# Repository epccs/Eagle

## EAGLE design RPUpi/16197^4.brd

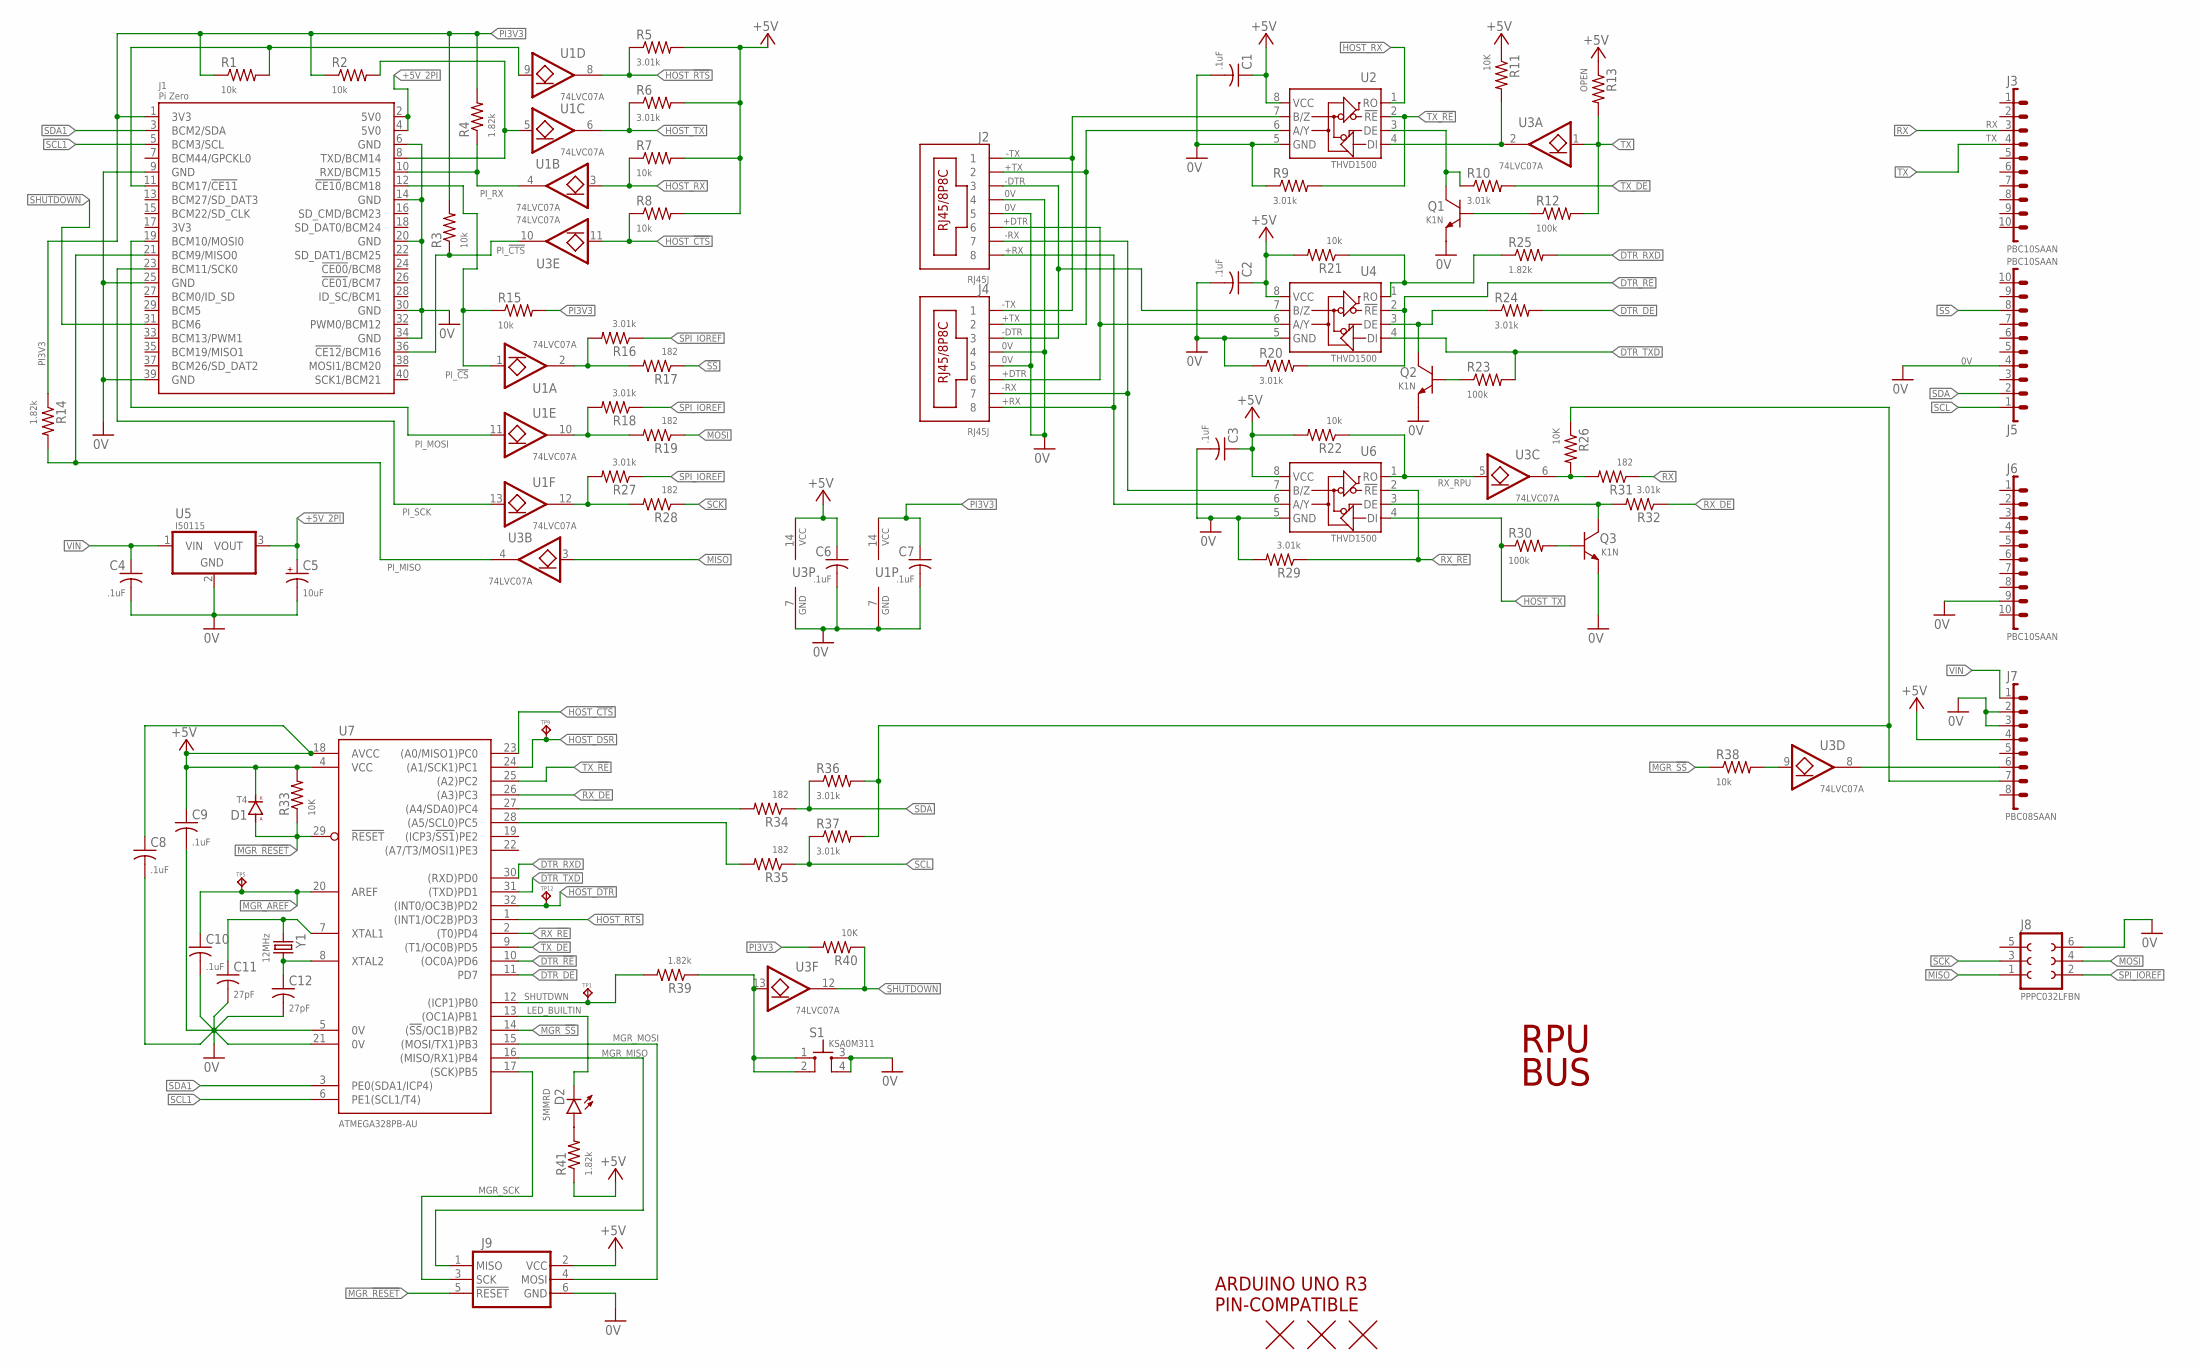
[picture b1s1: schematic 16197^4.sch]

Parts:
C1, C2, C3, C4, C6, C7, C8, C9, C10: .1uF; C0603(1608)
C5: 10uF; 3216
C11, C12: 27pF; C0603(1608)
D1: T4; SOD123
D2: 5MMRD; LED5MM
J1: Pi Zero; RASPI_ZERO_V40PIN
J2, J4: RJ45J; RJ45-8HZT
J3, J5, J6: PBC10SAAN; 1X10
J7: PBC08SAAN; 1X8
J8: PPPC032LFBN; F2X3
J9: ISP-SPIPTH; ISP
Q1, Q2, Q3: K1N; SOT23
R1, R2, R3, R7, R8, R15, R21, R22, R38: 10k; C0805(2012)
R4, R14, R25, R39, R41: 1.82k; C0805(2012)
R5, R6, R9, R10, R16, R18, R20, R24, R27, R29, R32, R36, R37: 3.01k; C0805(2012)
R11, R26, R33, R40: 10K; C0805(2012)
R12, R23, R30: 100k; C0805(2012)
R13: OPEN; C0805(2012)
R17, R19, R28, R31, R34, R35: 182; C0805(2012)
S1: KSA0M311; 0M311
TP1, TP5, TP9, TP12: TPPAD1-08; P1-08
U1, U3: 74LVC07A; 14SOIC
U2, U4, U6: THVD1500; SOIC8
U5: I50115; OKI-78SR-H
U7: ATMEGA328PB-AU; TQFP32-08
U$1: ARDUINO-UNO; ARDUINO_UNO
U$2, U$3, U$4: FIDUCIAL1.27; FIDUCIAL-1.27
Y1: 12MHz; CSM-3X

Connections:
0V: C1.2, C2.2, C3.2, C4.2, C5.-, C6.2, C7.2, C8.2, C9.2, C10.2, C11.2, C12.2, J1.6 (GND), J1.9 (GND), J1.14 (GND), J1.20 (GND), J1.25 (GND), J1.30 (GND), J1.34 (GND), J1.39 (GND), J2.4, J2.5, J4.4, J4.5, J5.4, J6.9, J7.2, J7.3, J8.6, J9.6 (GND), Q1.E, Q2.E, Q3.E, R9.1, R20.1, R29.2, S1.3, S1.4, U1.7 (GND), U2.5 (GND), U3.7 (GND), U4.5 (GND), U5.2 (GND), U6.5 (GND), U7.5 (0V), U7.21 (0V)
!RESET: J7.6, U3.8 (O)
!SS: J5.8, R17.1
+5V: C1.1, C2.1, C3.1, C6.1, C8.1, C9.1, D1.C (K), J7.4, J9.2 (VCC), R5.2, R6.2, R7.2, R8.2, R11.1, R13.1, R21.2, R22.2, R33.2, R41.1, U2.8 (VCC), U3.14 (VCC), U4.8 (VCC), U6.8 (VCC), U7.4 (VCC), U7.18 (AVCC)
+5V_2PI: C5.+, J1.2 (5V0), J1.4 (5V0), U5.3 (VOUT)
+DTR: J2.6, J4.6, U4.6 (A/Y)
+RX: J2.8, J4.8, U6.6 (A/Y)
+TX: J2.2, J4.2, U2.6 (A/Y)
-DTR: J2.3, J4.3, U4.7 (B/Z)
-RX: J2.7, J4.7, U6.7 (B/Z)
-TX: J2.1, J4.1, U2.7 (B/Z)
DTR_!RE: R20.2, U4.2 (!RE), U7.10 ((OC0A)PD6)
DTR_DE: R24.2, U7.11 (PD7)
DTR_RXD: R25.2, U7.30 ((RXD)PD0)
DTR_TXD: R23.2, U4.4 (DI), U7.31 ((TXD)PD1)
HOST_!CTS: R8.1, U3.11 (I), U7.23 ((A0/MISO1)PC0)
HOST_!DSR: TP9.TP, U7.24 ((A1/SCK1)PC1)
HOST_!DTR: TP12.TP, U7.32 ((INT0/OC3B)PD2)
HOST_!RTS: R5.1, U1.8 (O), U7.1 ((INT1/OC2B)PD3)
HOST_RX: R7.1, U1.3 (I), U2.1 (RO)
HOST_TX: R6.1, R30.1, U1.6 (O), U6.4 (DI)
IOREF: J7.7, R26.1, R36.2, R37.2
LED_BUILTIN: D2.K, U7.13 ((OC1A)PB1)
MGR_!RESET: D1.A, J9.5 (!RESET), R33.1, U7.29 (!RESET)
MGR_!SS!: R38.1, U7.14 ((!SS!/OC1B)PB2)
MGR_AREF: C10.1, TP5.TP, U7.20 (AREF)
MGR_MISO: J9.1 (MISO), U7.16 ((MISO/RX1)PB4)
MGR_MOSI: J9.4 (MOSI), U7.15 ((MOSI/TX1)PB3)
MGR_SCK: J9.3 (SCK), U7.17 ((SCK)PB5)
MISO: J8.1, U3.3 (I)
MOSI: J8.4, R19.1
unnamed: J1.8 (TXD/BCM14), R2.2, U1.5 (I)
unnamed: R38.2, U3.9 (I)
unnamed: R34.2, U7.27 ((A4/SDA0)PC4)
unnamed: J1.11 (BCM17/!CE11!), R1.2, U1.9 (I)
unnamed: R27.2, R28.2, U1.12 (O)
unnamed: R18.2, R19.2, U1.10 (O)
unnamed: R39.1, S1.1, S1.2, U3.13 (I)
unnamed: R35.2, U7.28 ((A5/SCL0)PC5)
unnamed: R16.2, R17.2, U1.2 (O)
unnamed: R26.2, R31.2, U3.6 (O)
unnamed: Q3.C, R32.2, U6.3 (DE)
unnamed: Q1.B, R12.1
unnamed: Q1.C, R10.1, U2.3 (DE)
unnamed: R21.1, R25.1, U4.1 (RO)
unnamed: Q2.C, R24.1, U4.3 (DE)
unnamed: Q2.B, R23.1
unnamed: Q3.B, R30.2
unnamed: D2.A, R41.2
PI3V3: C7.1, J1.1 (3V3), R1.1, R2.1, R3.2, R4.2, R14.1, R15.2, R40.2, U1.14 (VCC)
PI_!CS: J1.12 (!CE10!/BCM18), R15.1, U1.1 (I)
PI_!CTS: J1.36 (!CE12!/BCM16), R3.1, U3.10 (O)
PI_MISO: J1.21 (BCM9/MISO0), R14.2, U3.4 (O)
PI_MOSI: J1.19 (BCM10/MOSI0), U1.11 (I)
PI_RX: J1.10 (RXD/BCM15), R4.1, U1.4 (O)
PI_SCK: J1.23 (BCM11/SCK0), U1.13 (I)
RX: J3.3, R31.1
RX_!RE: R29.1, U6.2 (!RE), U7.2 ((T0)PD4)
RX_DE: R32.1, U7.26 ((A3)PC3)
RX_RPU: R22.1, U3.5 (I), U6.1 (RO)
SCK: J8.3, R28.1
SCL: J5.1, R35.1, R37.1
SCL1: J1.5 (BCM3/SCL), U7.6 (PE1(SCL1/T4))
SDA: J5.2, R34.1, R36.1
SDA1: J1.3 (BCM2/SDA), U7.3 (PE0(SDA1/ICP4))
SHUTDOWN: J1.31 (BCM6), R40.1, U3.12 (O)
SHUTDWN: R39.2, TP1.TP, U7.12 ((ICP1)PB0)
SPI_IOREF: J8.2, R16.1, R18.1, R27.1
TX: J3.4, R12.2, R13.2, U3.1 (I)
TX_!RE: R9.2, U2.2 (!RE), U7.25 ((A2)PC2)
TX_DE: R10.2, U7.9 ((T1/OC0B)PD5)
TX_RPU: R11.2, U2.4 (DI), U3.2 (O)
VIN: C4.1, J7.1, U5.1 (VIN)
XTAL1: C11.1, U7.7 (XTAL1), Y1.1
XTAL2: C12.1, U7.8 (XTAL2), Y1.2

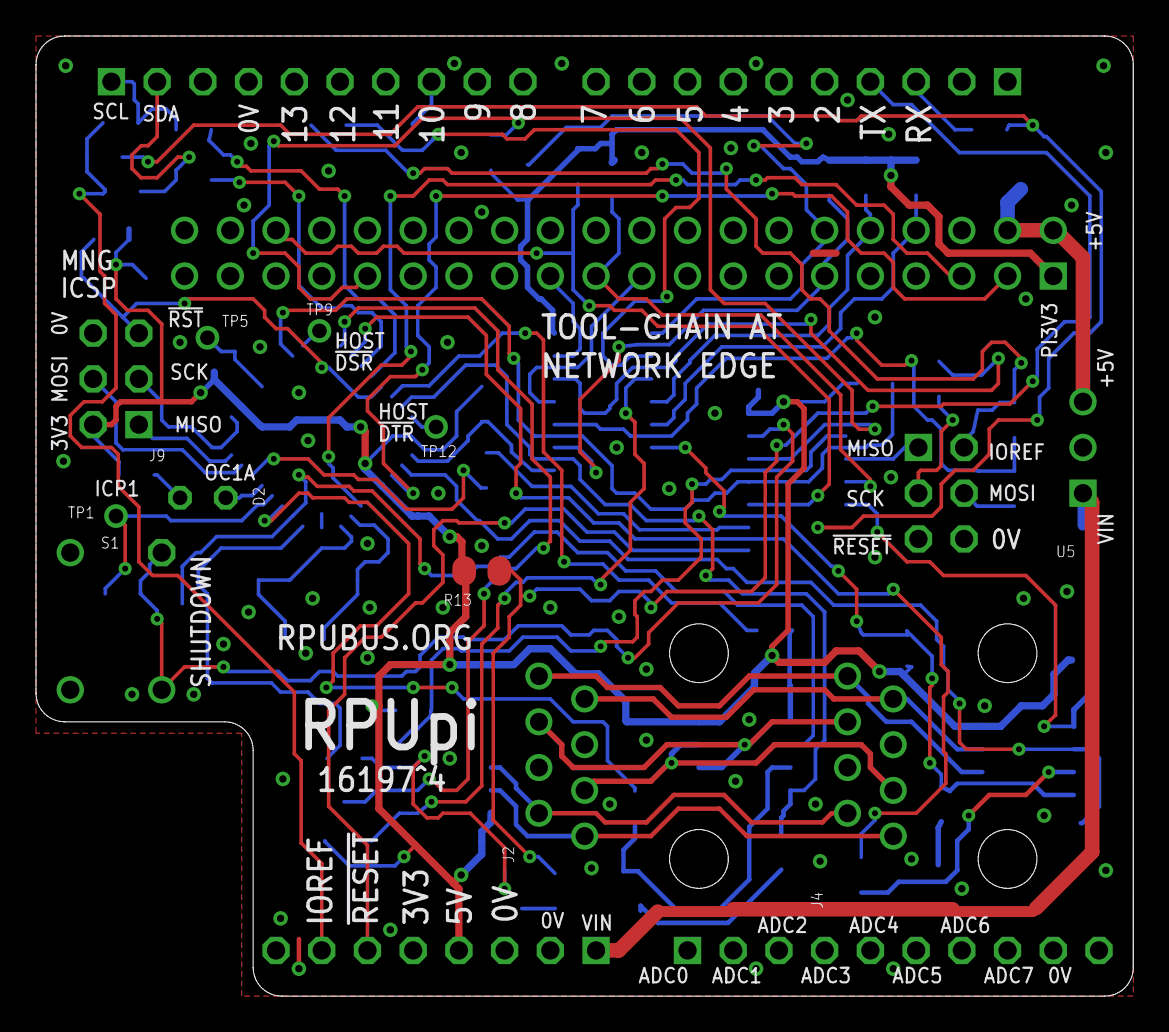
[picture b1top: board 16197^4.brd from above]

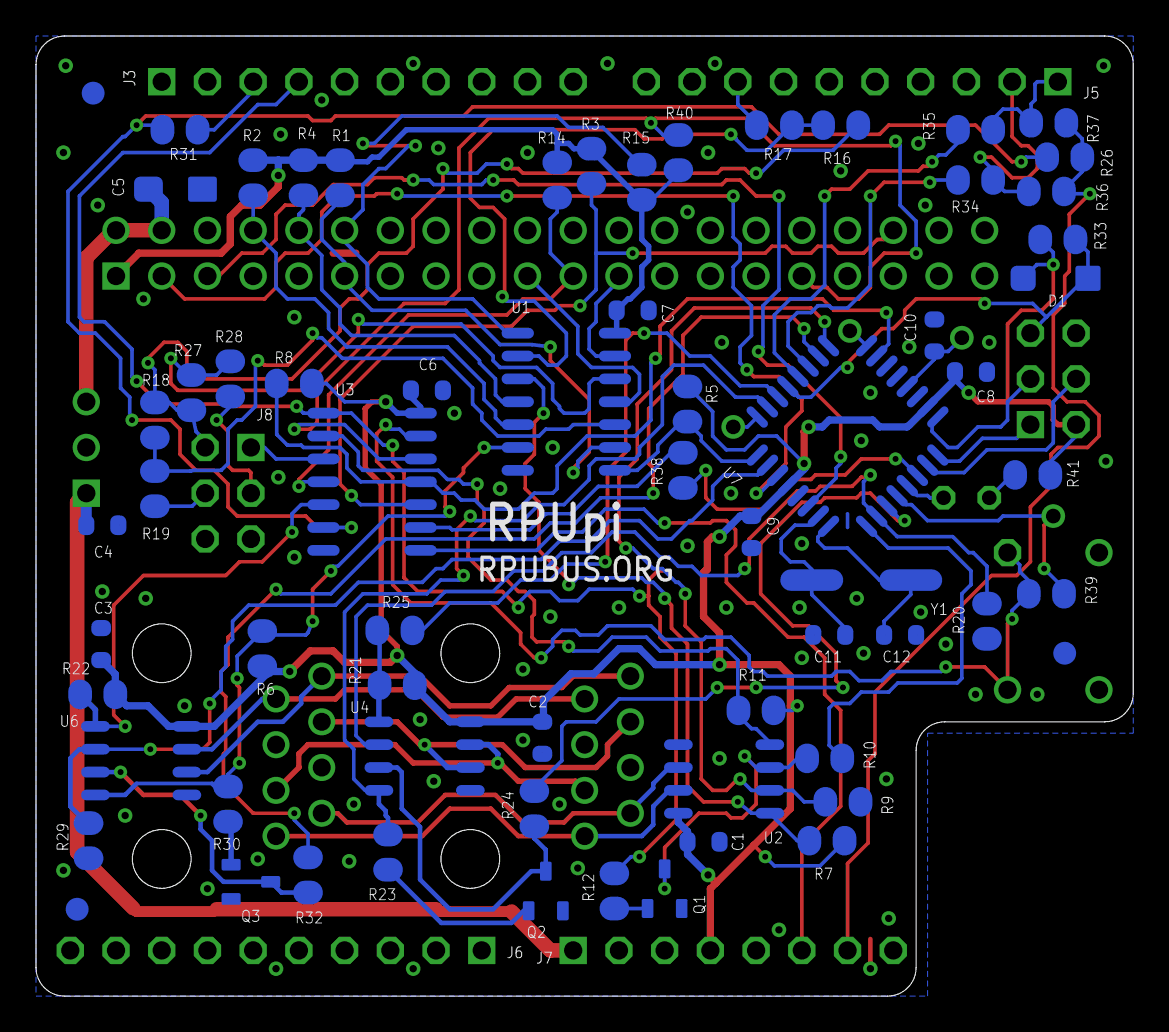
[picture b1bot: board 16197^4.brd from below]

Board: 2 copper layers, 61.0 x 53.3 mm, 84 parts (71 on the bottom side), 75 nets.

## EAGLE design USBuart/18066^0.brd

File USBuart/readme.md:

[USBuart]

USB UART bridge.

[USBuart]: https://github.com/epccs/Driver/tree/master/USBuart

The software for this will use the RPUftdi repo which will be renamed to USBuart.

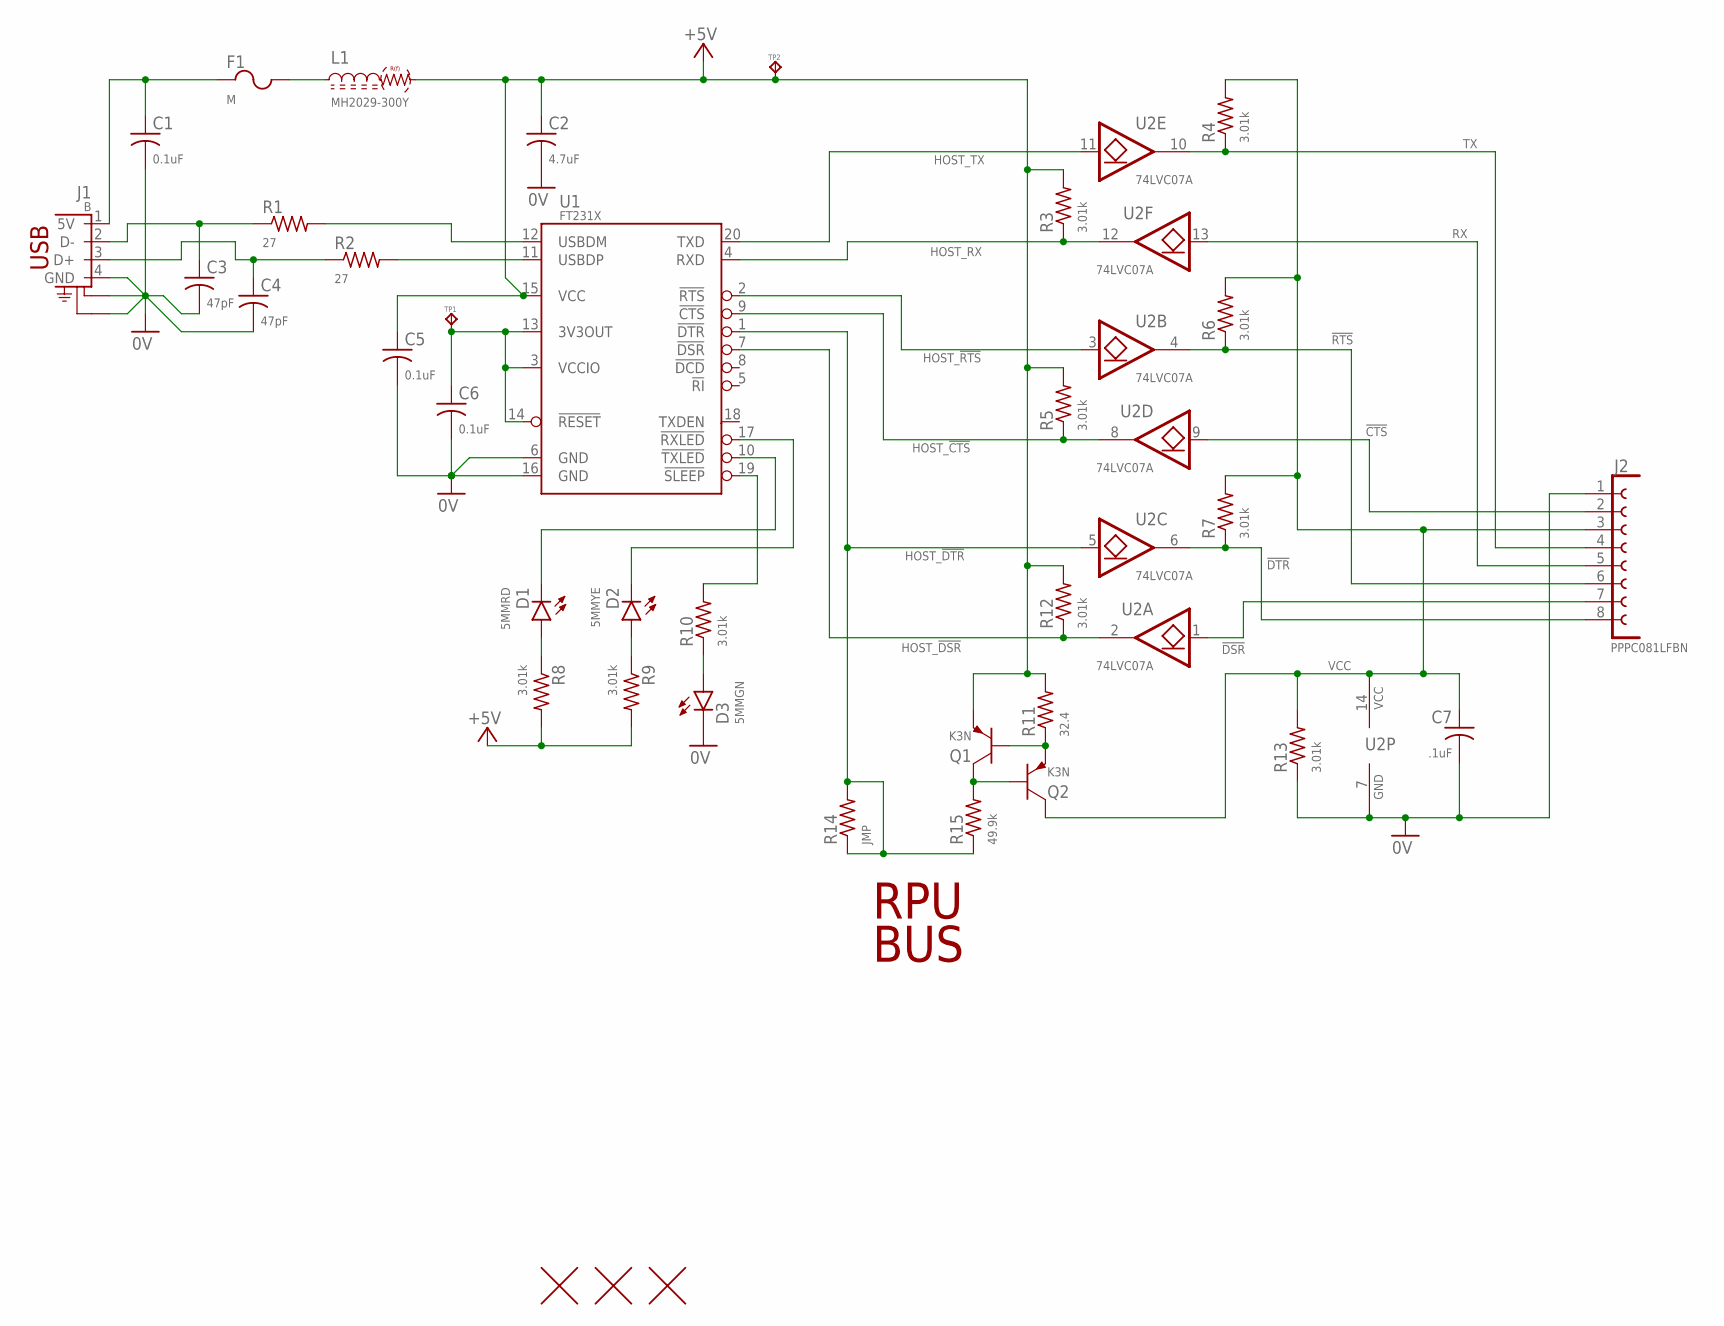
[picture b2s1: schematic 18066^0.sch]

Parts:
C1, C5, C6: 0.1uF; C0603(1608)
C2: 4.7uF; C1206(3216)
C3, C4: 47pF; C0603(1608)
C7: .1uF; C0603(1608)
D1: 5MMRD; LED5MM
D2: 5MMYE; LED5MM
D3: 5MMGN; LED5MM
F1: M; C1210(3225)
J1: B; USB-B-PTH
J2: PPPC081LFBN; F1X8
L1: MH2029-300Y; C0805(2012)
Q1, Q2: K3N; SOT23
R1, R2: 27; C0805(2012)
R3, R4, R5, R6, R7, R8, R9, R10, R12, R13: 3.01k; C0805(2012)
R11: 32.4; C0805(2012)
R14: JMP; C0805(2012)
R15: 49.9k; C0805(2012)
TP1, TP2: TPPAD1-08; P1-08
U1: FT231X; 20SSOP
U2: 74LVC07A; 14SOIC
U$2, U$3, U$4: FIDUCIAL1.27; FIDUCIAL-1.27

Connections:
0V: C1.2, C2.2, C3.2, C4.2, C5.2, C6.2, C7.2, D3.K, J1.4 (GND), J1.S1 (CHASSIS1), J1.S2 (CHASSIS2), J2.1, R13.1, U1.6 (GND), U1.16 (GND), U2.7 (GND)
!CTS: J2.2, U2.9 (I)
!DSR: J2.7, U2.1 (I)
!DTR: J2.8, R7.1, U2.6 (O)
!RTS: J2.6, R6.1, U2.4 (O)
+5V: C2.1, C5.1, L1.2, Q1.E, R3.2, R5.2, R8.2, R9.2, R11.2, R12.2, TP2.TP, U1.15 (VCC)
D+: C4.1, J1.3 (D+), R2.1
D-: C3.1, J1.2 (D-), R1.1
FT3V3: C6.1, TP1.TP, U1.3 (VCCIO), U1.13 (3V3OUT), U1.14 (!RESET!)
HOST_!CTS: R5.1, U1.9 (!CTS!), U2.8 (O)
HOST_!DSR: R12.1, U1.7 (!DSR!), U2.2 (O)
HOST_!DTR: R14.1, R14.2, R15.1, U1.1 (!DTR!), U2.5 (I)
HOST_!RTS: U1.2 (!RTS!), U2.3 (I)
HOST_RX: R3.1, U1.4 (RXD), U2.12 (O)
HOST_TX: U1.20 (TXD), U2.11 (I)
unnamed: Q1.B, Q2.E, R11.1
unnamed: C1.1, F1.1, J1.1 (5V)
unnamed: F1.2, L1.1
unnamed: D2.A, R9.1
unnamed: D1.K, U1.10 (!TXLED)
unnamed: D2.K, U1.17 (!RXLED)
unnamed: Q1.C, Q2.B, R15.2
unnamed: R1.2, U1.12 (USBDM)
unnamed: R2.2, U1.11 (USBDP)
unnamed: D3.A, R10.1
unnamed: D1.A, R8.1
unnamed: R10.2, U1.19 (!SLEEP)
RX: J2.5, U2.13 (I)
TX: J2.4, R4.1, U2.10 (O)
VCC: C7.1, J2.3, Q2.C, R4.2, R6.2, R7.2, R13.2, U2.14 (VCC)

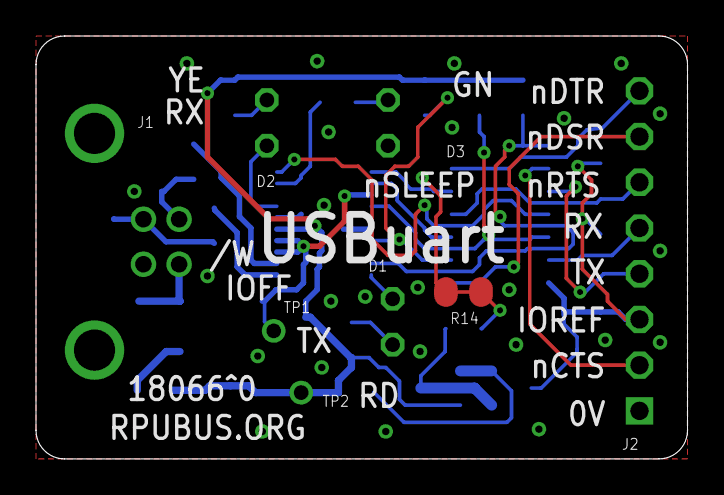
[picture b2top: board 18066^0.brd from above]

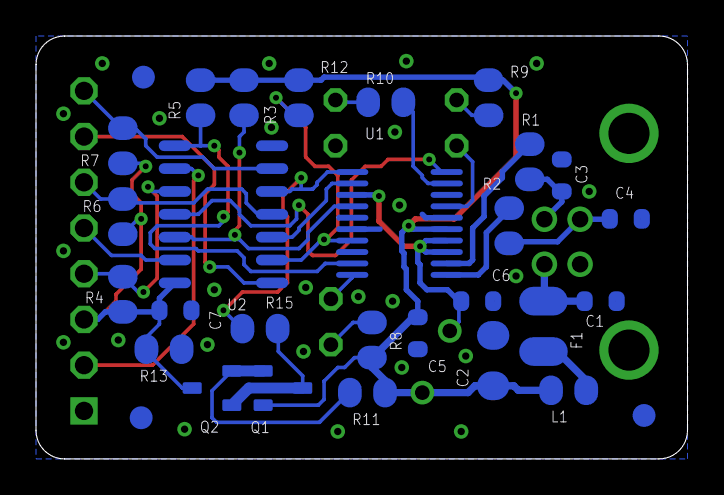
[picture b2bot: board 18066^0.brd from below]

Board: 2 copper layers, 36.2 x 23.5 mm, 38 parts (30 on the bottom side), 30 nets.

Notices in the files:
parts and their libraries:
P-DCDC: Copyright (C) 2013 Ronald Steven Sutherland
under the terms of the GNU Free Documentation License, Version 1.2 or
any later version published by the Free Software Foundation; with no
C-C: Released under the Creative Commons
Attribution Share-Alike 3.0 License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
